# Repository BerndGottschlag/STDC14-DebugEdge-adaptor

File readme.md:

# Description

This part is an adapter from the STDC14 of the STLINK_V3MINI to
  - the [DebugEdge interface](https://github.com/debug-edge/DebugEdge) and
  - one version of the interface used by the ST-Link V2 clones.

# License

The design is licensed under the [CERN Open Hardware Licence Version 2 - Permissive](cern-ohl_p_v2.txt).

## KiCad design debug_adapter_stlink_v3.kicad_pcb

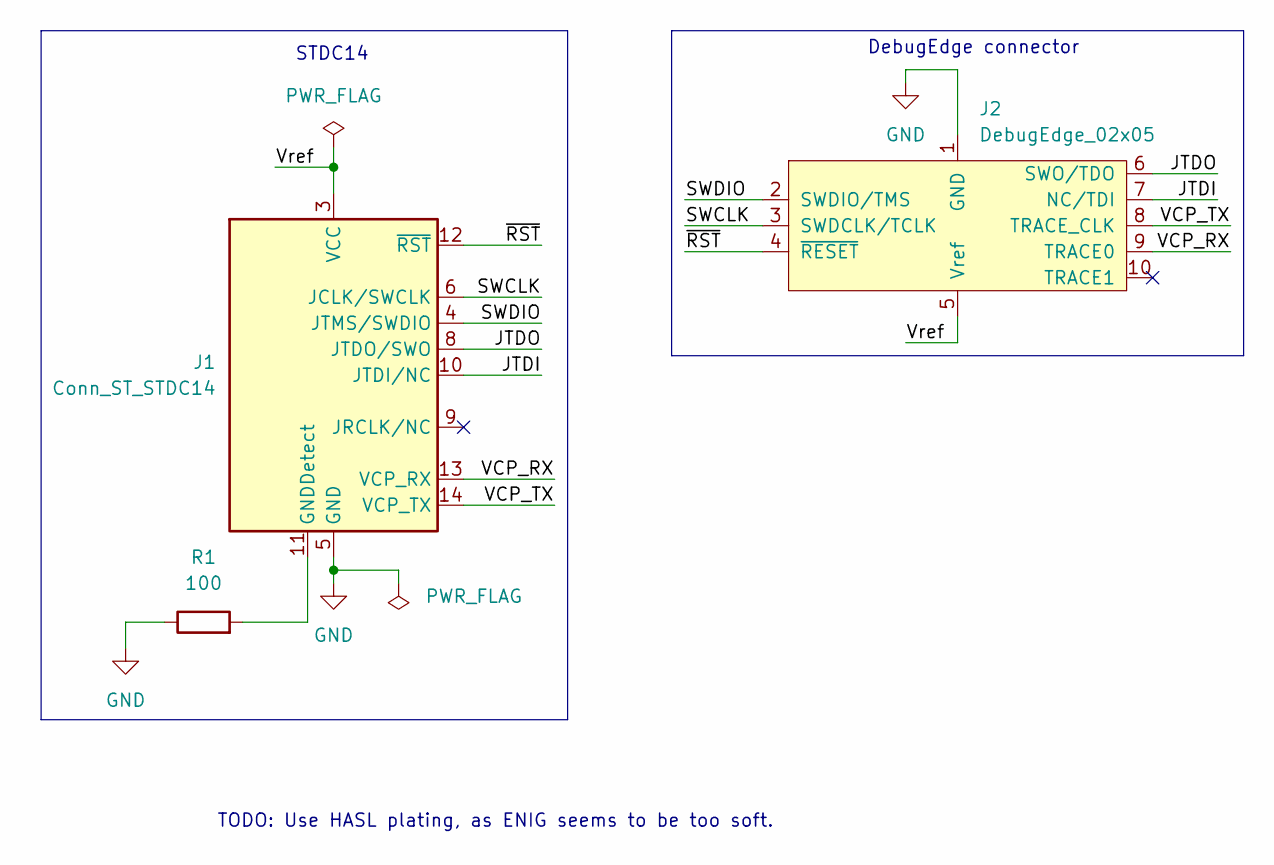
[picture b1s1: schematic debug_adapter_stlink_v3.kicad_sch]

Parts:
J1: Conn_ST_STDC14; cnc_tech_3221-14-0100-00
J2: DebugEdge_02x05; DebugEdge_2x05_Host
R1: 100; R_0805_2012Metric_Pad1.20x1.40mm_HandSolder

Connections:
/JTDI: J1.10 (JTDI/NC), J2.7 (NC/TDI)
/JTDO: J1.8 (JTDO/SWO), J2.6 (SWO/TDO)
/SWCLK: J1.6 (JCLK/SWCLK), J2.3 (SWDCLK/TCLK)
/SWDIO: J1.4 (JTMS/SWDIO), J2.2 (SWDIO/TMS)
/VCP_RX: J1.13 (VCP_RX), J2.9 (TRACE0)
/VCP_TX: J1.14 (VCP_TX), J2.8 (TRACE_CLK)
/Vref: J1.3 (VCC), J2.5 (Vref)
/~RST: J1.12 (~RST), J2.4 (~RESET)
GND: J1.5 (GND), J1.7 (GND), J2.1 (GND), R1.1
unnamed: J1.11 (GNDDetect), R1.2

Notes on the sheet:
TODO: Use HASL plating, as ENIG seems to be too soft.
DebugEdge connector
STDC14

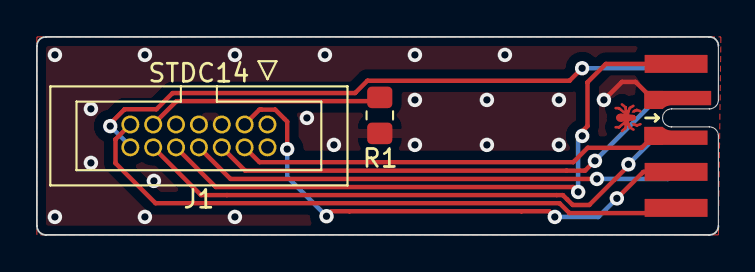
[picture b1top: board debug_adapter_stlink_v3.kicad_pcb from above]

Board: 2 copper layers, 37.9 x 11.0 mm, 3 parts (0 on the bottom side), 10 nets.

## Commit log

2022-04-24 First version of the design
2022-04-24 Update the license
2022-04-24 Add exports folder to the .gitignore
2022-04-24 Remove the ST-Link-v2-clone connector
    Reason: The adaptor for the ST-Link-V2 clone connector will be
    implemented as its own PCB.
